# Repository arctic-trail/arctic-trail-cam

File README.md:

# Arctic Trail Cam System

> **Open-source, RF-silent Arctic trail & cabin camera with a 1-way optical fiber diode and `<4mW` cold-boot gatekeeper. A private, pro-bono free-market COTS build. 🇫🇮 Finnish engineering.**
>
> * **GitHub Topics:** `raspberry-pi-5` · `rp2350` · `pico-2` · `hailo-8l` · `plutosdr` · `software-defined-radio` · `troposcatter` · `data-diode` · `fiber-optics` · `bvlos` · `acoustic-sensing` · `micro-doppler` · `ed25519` · `edge-ai` · `cots` · `open-hardware` · `trail-camera` · `finland` · `nordic` · `baltic`
> * **Visual Architecture & Engineering Overview (27-Slide PDF Deck):** [`ARCTIC_TRAIL_CAM_EXECUTIVE_OVERVIEW.pdf`](ARCTIC_TRAIL_CAM_EXECUTIVE_OVERVIEW.pdf)
> * **Complete Illustrated IKEA-Style Build Manual (PDF Booklet):** [`ARCTIC_TRAIL_CAM_BUILD_AND_FIELD_GUIDE.pdf`](ARCTIC_TRAIL_CAM_BUILD_AND_FIELD_GUIDE.pdf)
> * **Sister Project (Autonomous Wilderness Search-and-Rescue Drone, Heated Launch Nest & Maritime USV Autonomy):** [`arctic-trail/karhunkierros-sar-drone`](https://github.com/arctic-trail/karhunkierros-sar-drone)
> * **FIN-LAB COTS Airspace-Safety, Maritime & Corridor Enabler Suite (`FIN-SIG-LIB v1.0` `#4`, `[P12-BELT]` & `[P12-URBAN]` Non-RF Corridor/Bridge/Substation Sensing `#7`, `FIN-LAB-06` `1.85 m` Inshore & `FIN-LAB-06B` `3.60 m` Offshore Sea-State-5 Cable-Inspection USVs `#12`, `[P11-COAST-2KM]` `1–2.5 km` Gimbal-Free Optical Strait Bridge, and `[P21-SVALBARD]` Treeless Permafrost Cairn Kit):** [`pi-diode-trailcam/pi5_sender_node/northern_flank_red_gap_solver.py`](pi-diode-trailcam/pi5_sender_node/northern_flank_red_gap_solver.py)
> * **License:** [`MIT License`](LICENSE)

> **🛠️ PLEASE FORK, BUILD, BREAK & IMPROVE THIS (NO PERMISSION NEEDED)**
> These repositories are **100% open-source (`MIT License`) public-good engineering** for harsh Nordic & Baltic conditions.
> * **No ego, no gatekeeping:** You do **not** need to ask permission to fork this, build a module on your kitchen table, use it for a university course/thesis, or spin a commercial product out of it.
> * **Test logs > theory:** Almost everything here is currently at bench/simulation stage. If you build a €68 acoustic pod, freeze a battery at `-25 °C`, or 3D-print a sub-scale airframe and prove our numbers wrong—**please open a Pull Request or Issue with your real-world data!**
> * **100% Civilian & Legal to Tinker With:** Everything in these repos (weather/wildlife nodes, optical diodes, airport/corridor acoustic logging, SAR navigation, cooperative own-drone soft-net recovery) is strictly civilian and legal for students, hobbyists, and labs to build and test. While the harsh-environment resilience techniques explored here—such as zero-RF optical fiber links, GNSS-denied navigation, acoustic/micro-Doppler drone detection, and low-cost COTS modular packaging—draw technical inspiration from drone and sensor technology widely seen in Ukraine and on public media, the **intended use case of this project is 100% civilian**.

> [!WARNING]
> **PROTOTYPE DISCLAIMER — ACTIVE DEVELOPMENT & BENCHTOP TESTING IN PROGRESS (`v0.9-beta`)**
> * **Under Active Development:** This repository is an **experimental proof-of-concept hardware & software engineering prototype** currently undergoing physical benchtop integration and staged validation.
> * **Validated vs. Target Metrics:** All software/firmware state machines (`Pico 2` Gatekeeper, `Pi 5` sender node, `Ed25519` + `1×2` optical diode UDP pipeline, and `5/5` automated simulation & DRC test suites) are implemented and verified in simulation and Stage 1–3 benchtop bring-up. System performance figures—including the **`6.4–6.8 s` cold-boot latency** (`<150 ms` with SPI Instant-Snap buffer) and **`1.0 to 2.5+ year` (`365–900+ day`) battery life** (at a realistic `10 captures/month` with a drop-in `LiFePO4` / AGM battery, or `4–10+ months` on busy `10 captures/day` trails)—are **engineering design targets and theoretical power/link-budget projections** currently undergoing physical measurement.
> * **Ongoing Defect Tracking & Field Reports:** Hardware, firmware, and mechanical defects discovered during benchtop and outdoor trials are actively being fixed. Measured real-world latency logs, false-alarm soak results, and battery discharge telemetry will be published here as testing progresses.

An off-grid, event-triggered movement-detection and trail camera system (**Arctic Trail Cam System** / `pi-diode-trailcam` & `sky-diode-relay`) designed for remote cabins, hunting grounds, and private forest lands far from internet or cellular coverage. Engineered for year-round operation in harsh Finnish Arctic conditions (`-40°C` to `+50°C`), the system combines milliwatt standby sensing (`Raspberry Pi Pico 2` Gatekeeper), 6-second cold-boot AI vision (`Raspberry Pi 5` + `Sony IMX708 NoIR`), and **physics-enforced one-way optical transmission** (`Ed25519`-signed `1080p` JPEGs sent over `3 mm` moss-buried armored glass fiber or an invisible infrared light beam) with **zero radio emissions (`0.00 W RF`)** at the camera tree.

> [!IMPORTANT]
> **Project Ethos — Private, Pro-Bono Free-Market Engineering ([`MIT License`](LICENSE)):**
> Rather than relying on `$15,000+` proprietary industrial sensors or cloud-tethered cellular cameras that broadcast detectable radio beacons and die in freezing `-30°C` winters, this project explores how **standard commercial off-the-shelf (COTS) components (`$233.37` benchtop / `$598.20` complete turnkey field system including all power supplies, USB/SD adapters, and Cat6/fiber cables)** can be assembled by any cabin owner, hunter, landowner, or researcher:
> 1. **100% Retail COTS Supply Chain:** Built from standard parts on Amazon, Adafruit, DigiKey, Mouser, or Motonet/Verkkokauppa.com in Finland.
> 2. **Zero Cloud Subscriptions & Zero Radio Signature:** No monthly fees, no cellular SIM cards, and zero Wi-Fi/Bluetooth beacons.
> 3. **"IKEA-Simple" Reproducibility:** Every breadboard hole, jumper wire, and enclosure hole-saw cut is illustrated step by step.
> 4. **Single-Source-of-Truth (`SSOT`) Documentation:** Each guide in this repository owns one distinct topic without duplicating tables or instructions across files (see [Documentation Map](#single-source-of-truth-ssot-documentation-map) below).

---

## 1. System Performance & Battery Life Expectations (At a Glance)

Detailed seasonal power models and component-level current draws are maintained in **[`HARDWARE_SPECS_AND_BOM.md`](pi-diode-trailcam/docs/HARDWARE_SPECS_AND_BOM.md#1-system-performance-expectations--cold-boot-latency-spec)**.

| Performance Parameter | Verified / Target Specification | Operating Context |
| :--- | :--- | :--- |
| **Multi-Year Battery Life (Drop-In `12V 15Ah–24Ah` `LiFePO4` / `60Ah` External)** | **At `10 Photos/Month` *(Realistic Cabin / Border Trail)*:**<br>• **`1.5 – 2.5+ Years` (`565 – 900+ Days`)** *(Drop-In `15Ah–24Ah LiFePO4` inside vault)*<br>• **`3.0 – 4.0+ Years`** *(External `60Ah` Battery — self-discharge limited)*<br>**At `10 Photos/Day` (`300/Month` *High-Traffic Trail*):**<br>• **`10 – 16+ Months`** *(`15Ah–24Ah LiFePO4`)* / **`1.8 – 2.5+ Years`** *(`60Ah`)* | At `10 photos/month` (`0.33/day`), active capture energy is negligible (`~0.01 Wh/day`), so total draw with `4–12 mW` Eco Gatekeeper standby is just `~0.15–0.30 Wh/day`. |
| **Battery Life (Standard `12V 12Ah` AGM `[P17]`, `$29` / `€27`)** | **At `10 Photos/Month`:** **`1.0 – 1.3+ Years` (`365 – 480 Days`)** *(3-Season)* / **`9 – 12 Months` (`270 – 365 Days`)** *(Finnish Winter under moss)*<br>**At `10 Photos/Day`:** **`120 – 220+ Days`** | Included baseline `12V 12Ah` sealed AGM battery (`[P17]`) mounted inside the moss-buried `QILIPSU` Base Vault (`[P21]`). |
| **Standby Power (`Domain A` Always-On)** | **`3.8 mW – 12.0 mW`** *(Eco Gatekeeper)* / **`~38 mW`** *(Radar Micro-Sweep)* | `Raspberry Pi 5 [P01]` and `StarTech Fiber Converter [P13]` are **100% physically powered off (`0.00 W`)** by the high-side relay `99.9%` of the time. |
| **Cold-Boot Trigger-to-Photo Latency** | **`6.4 – 6.8 seconds` total** (`0.025 Wh` per capture) | `Pico 2` switches on `Domain B` $\rightarrow$ `Pi 5` boots stripped Linux kernel in `3.8s` $\rightarrow$ captures `1080p` JPEG $\rightarrow$ runs AI detection $\rightarrow$ signs (`Ed25519`) & blasts `3×` over optical fiber $\rightarrow$ cuts power back to `0.00 W`. |
| **Operating Temperature & Weatherproofing** | **`-40°C` to `+50°C` Year-Round (`IP67` / `IP68`)** | Moss-buried `QILIPSU` vault buffers battery at `-2°C to -8°C` in deep winter; `3.6W` PTC window heater clears lens frost in `4.0s`. |
| **Detection & Night-Vision Range** | **`15 m – 60 m` approach** (`25°` oblique trail aim)<br>**`25 m – 80 m` in dense off-trail spruce forest** (`0.6–0.9 m` under-canopy trunk tunnel)<br>**`8 m – 18 m` night IR** (`940 nm` invisible LEDs, zero red glow) | Multi-modal wake cascade (`QMC5883L` magnetometer [`0 dB` wood loss] + `HLK-LD2450` `24 GHz` radar + optional `SM-24` root-mat geophone [`25–60 m` footsteps] & `[P11-AIR]` acoustic diffraction [`35–80 m`] around trunks; see [`ASSEMBLY_GUIDE.md`](pi-diode-trailcam/docs/ASSEMBLY_GUIDE.md#step-61--strap-zone-1-to-the-pine-trunk--bury--insulate-zone-3-underground)). |
| **Link Reach (`Fiber`, `Collimator`, or `Sky-Relay`)** | **`30 m – 10 km`** *(Moss-Buried Armored OS2 Glass Fiber)*<br>**`10 m – 100 m`** *(Water-Strait `1310 nm` Collimator Laser Bridge)*<br>**`200 m – 20 km`** *(All-Weather `2.4 GHz` Troposcatter & Canopy-Bounce Relay — [`sky-diode-relay`](sky-diode-relay/README.md) `Build D`)* | Physical one-way optical data diode (`1×2` optical splitter loopback trick at camera; cabin receiver `TX` port physically unpatched and capped) or one-way `VK7MO` Keyed-FHSS Troposcatter (`+14.1 dB` to `+62.3 dB` all-weather SNR). |

### 1.1 Readiness Matrix, Known Unknowns & Unvalidated Physical Assumptions

To help external evaluators, builders, and researchers assess this project objectively, the table below separates **what has been physically built and bench-verified** from the **key physical unknowns** that remain unproven until freezer and outdoor field trials (`Stages 4–6`) are completed:

| Subsystem / Claim | Built & Verified on Indoor Bench? | Simulated & Unit-Tested? | Field-Validated Outdoors? | Primary Real-World Failure Risk / Unknown | Planned Validation Gate |
| :--- | :---: | :---: | :---: | :--- | :--- |
| **`Pico 2` Gatekeeper + `GY-271` (`0x2c`) + `Pi 5` + `IMX708` + `1×2` Optical Fiber Diode (`Stages 1–3`)** | **Yes** (`Photos 1–72` live bench build) | **Yes** (`5/5` suites) | **No** (indoor bench only) | Mechanical vibration loosening breadboard jumpers or ZIF ribbons during transport if the 3-step `Permatex 81158` silicone + `3M` block lock is skipped. | **Stage 4–5:** Enclosure integration, vibration lock, and `48-hour` outdoor soak. |
| **`6.4 – 6.8 s` Cold-Boot Trigger-to-Photo Latency** | **Partial** (standard Raspbian boot verified; stripped initramfs modelled) | **Yes** | **No** | Standard Debian Bookworm boots in `~12–18 s`; achieving `6.4 s` in hardware requires tuning the stripped kernel/initramfs (`quiet fastboot`) and verifying that cold `-20 °C` battery internal resistance ($I\cdot R$ drop) does not brown out the `5V/5A` buck during `Pi 5` + `StarTech` inrush. | **Stage 5 & Freezer Gate:** Oscilloscope/multimeter inrush voltage check at `-18 °C` (`4-hour` freezer test). |
| **`1.0 – 2.5+ Year` Battery Life & `3.8 mW` Standby Draw** | **No** (power switches `[P12]` in hand; long-term discharge modelled) | **Yes** (seasonal power model) | **No** | Elevated quiescent leakage in budget buck converters (`DIANN` / `5A USB-C` buck), frequent false wakes from wind-blown branches on the `24 GHz` radar (`HLK-LD2450`), or unburied `-30 °C` AGM electrolyte freezing can cut real battery life by `50–80%`. | **Stage 5:** Multimeter microamp standby measurement across `Domain A/B` + `48-hour` wind false-alarm soak. |
| **`sky-diode-relay` `Build D` (`200 m – 20 km` NLOS Troposcatter / Canopy-Bounce)** | **Parts 100% In Stock** (`PlutoSDR`, `SE2576L` PA, `SKY65405` LNA, `VBF-2435+`, `HG2414P`) | **Yes** (`24/24` channel & FEC suites) | **No** (`0 km` outdoor RF test to date) | Real granite ridge diffraction profiles, wet heavy snow on conifer needles (`ITU-R P.833`), or local `2.4 GHz` noise floors higher than modelled can reduce the theoretical `+14.1 dB` worst-case SNR margin at `20 km`. | **Build D Field Trial:** Progressive `500 m` $\to$ `2 km` $\to$ `10–20 km` NLOS link-margin walk test. |
| **`[P11-AIR]` Acoustic/Micro-Doppler & `[P12-BELT]` Corridor Classifiers** | **No** (algorithmic & signature models in `northern_flank_red_gap_solver.py`) | **Yes** (`FIN-SIG-LIB v1.0`) | **No** | Heavy wind roar in pine crowns (`> 12 m/s`), freezing rain on MEMS microphone ports (`IM69D130`), or highway traffic acoustics can raise false-alarm rates above the modelled `≤ 25%` ceiling. | **Acoustic Field Gate:** Outdoor winter recordings with wind-muff hydrophobic membranes. |

---

## 2. Device in Context: 3-Zone Pine Tree Unit & `200 m – 20 km` Troposcatter / Beam Relay

Detailed exterior/interior cutaway plates for **Device 1 (`Zone 1` Camera/Radar Pod)**, **Device 2 (`Zone 3` Base Vault)**, **Device 3 (Cabin & Woods Collectors)**, and the **Scenario A / B1 / B2 / B3** deployment comparison are included in **[`ASSEMBLY_GUIDE.md`](pi-diode-trailcam/docs/ASSEMBLY_GUIDE.md)**.

### 2.1 The 3-Zone Covert Split-Pod Camera Unit on a Forest Pine Tree

* **Zone 1 (Top — `2.0 m` High in Pine Bark Crevice):** Fist-sized `Hammond 1591BSBK` (`112 × 62 × 31 mm`, factory `IP54` sealed with a perimeter `Permatex 81158` lid-channel gasket, or drop-in `Hammond 1554EGY` factory `IP68`) pod with **only one circular `20 mm` (`[T06]` cone step bit) or `28 mm` (`[T05]` hole saw) glass window** (`IMX708` camera locked to `AfMode=0, LensPosition=0.5` hyperfocal focus + black neoprene foam anti-glare baffle + `2× 940 nm` stealth IR LEDs + `39-Ohm 5W` [`3.69 W` @ `12V`] de-icer) and an internal `HLK-LD2450` `24 GHz` radar shooting cleanly through the solid, uncut lower ABS wall.
* **Zone 2 (Middle — `2.0 m` Trunk Cord):** Shielded `Arducam CSI-to-HDMI` (`2.0 m`) + 4-wire radar/heater umbilical wrapped in `Gear Aid Camo Form` matte bark tape tucked into a natural vertical bark groove.
* **Zone 3 (Bottom — Buried `20–30 cm` Underground & Foam-Insulated at Tree Roots):** Waterproof `QILIPSU IP67` (`285 × 195 × 130 mm`) vault housing the wall-to-wall `12V 12Ah` battery (`[P17]`), `Pico 2` Gatekeeper (`[P07]`), `5V` buck/relay power switches (`[P12]`), `Raspberry Pi 5` (`[P01]`), and `1310 nm` `StarTech` Media Converter + `1×2` Optical Splitter Diode (`[P13]`–`[P15]`).
  * **Cold-Weather Survival WITH vs. WITHOUT Underground Burial & Foam Insulation:** The tree-mounted **Zone 1 Micro-Pod** contains only solid-state silicon + the `3.69 W` ceramic window de-icer (`[P12-HEAT]`) and operates in open air down to **`-35°C to -40°C`**. For the **Zone 3 Base Vault**: **WITHOUT underground burial or foam insulation** (sitting above ground in open air with standard `12Ah` AGM `[P17]`), reliable operation is limited to **`-15°C to -20°C`** (`45%–55%` battery capacity; risk of `Pi 5` boot brownout or electrolyte freeze below `-22°C`, or **`-25°C to -28°C`** if fitted with the `10–20 mm` foam liner + `[P21-FROST]` supercap buffer on bare rock). **WITH `20–30 cm` underground burial + `10–20 mm` closed-cell XPS/neoprene foam insulation + moss/snow cover**, geothermal subsoil warmth keeps the internal battery bay at **`-2°C to -8°C`** even when outside air plunges to **`-35°C to -40°C`** (**`-45°C`** under `30+ cm` snowpack), preserving **`85%–92%` battery capacity** (`1.2–2.5+ years` with `LiFePO4`).

### 2.2 The `200 m – 20 km` Non-Line-of-Sight Troposcatter & Water-Crossing Beam System ([`sky-diode-relay`](sky-diode-relay/README.md))

* **Ordered Production Baseline (`Build D` — `200 m to 20 km` All-Weather `2.4 GHz` Troposcatter, Hydrometeor & Canopy-Bounce Relay, `$1,341.94` parts subtotal, `~35–45 min` zero-solder assembly):** Uses **Analog Devices `ADALM-PLUTO` SDRs**, a **Skyworks `SE2576L-EK1` `1.0 W` (`+30 dBm`) PA (`PA_EN` driven strictly at `3.3 V` from `Pico 2 GP3`)**, a **Skyworks `SKY65405-21EK1` (`1.2 dB NF`) LNA (`VEN` driven strictly at `3.3 V` from `Pico 2 3V3_OUT`)**, **Mini-Circuits `VBF-2435+` (`2370–2500 MHz`) coaxial bandpass filters**, and **L-com `HG2414P` (`14 dBi`) outdoor flat-panel antennas** to bounce `VK7MO` coherent lock-in frames (`+55.8 dB` processing gain) off lower-troposphere refractivity gradients, rain/snow clouds, and forest canopies over granite hills (`+14.1 dB` to `+62.3 dB` SNR across all 5 Finnish weather regimes). Protected by a **6-layer electronic anti-jamming stack** that hops into out-of-ISM guard bands (`2380.373 MHz` & `2487.818 MHz`) outside consumer Wi-Fi/drone jammers.
  * **⚠️ Regulatory Disclaimer & `--civilian-eu-compliant` Software Flag (Zero Hardware Changes):** Operating `Build D` at full `1.0 W` (`+42.5 dBm` / `17.8 W` EIRP) or hopping into out-of-ISM guard bands (`2370–2400 MHz` / `2483.5–2500 MHz`) **requires a Traficom experimental/test radio license, public-safety / emergency authority authorization, or Amateur Radio permit (`13 cm` band, `2300–2450 MHz`)**. For **license-exempt peacetime civilian operation** under Traficom Regulation 15 / EU ETSI EN 300 328, pass **`--civilian-eu-compliant`** (`civilian_eu_compliant=True`) to `sky_transmitter.py` and `sky_receiver.py`: this restricts all FHSS carrier hops strictly inside **`2400.0–2483.5 MHz`** (`2402–2480 MHz`) and disables/attenuates the PA (`pa_gate_gp3=0`, `+7.5 dBm` SDR output) so total radiated power is capped at **`<= +20.0 dBm` (`100 mW` EIRP)** while still bridging multi-kilometer NLOS forest paths via `VK7MO`'s `+55.8 dB` coherent processing gain.
* **Short-Range Optical Beam (`Scenario B2` — `10 m to 100 m` Across a Lake Strait or Road):** Two shore-mounted `1310 nm` fiber lens collimators (**Thorlabs `F220FC-1310`**) convert the fiber signal into a pencil-thin, invisible infrared laser beam across water channels where boats or winter ice prevent laying cable (with optical reference builds `A/B/C` also supported in [`sky-diode-relay`](sky-diode-relay/README.md)).

### 2.3 The Cabin Collector Hub & 3D Evidence Console ([`dashboard_server.py`](pi-diode-trailcam/collector_hub/dashboard_server.py) / [`ui/index.html`](pi-diode-trailcam/collector_hub/ui/index.html))

* **100% Offline Local Browser Console (`http://localhost:8080` / `8123`):** Streams `Ed25519`-verified JPEGs (`DD\x02` chunks), AI bounding boxes (`Hailo-8L` / `YOLOv8n ONNX`), `<150 ms` `Pico 2` SPI First-Frame Instant-Snap PIP insets, and 6-cell `Pico 2` sensor telemetry (`MAG ΔB`, `SEISMIC RMS`, `RADAR DIST/SPD`, `NODE TEMP`, `UPTIME`, `PROFILE`) alongside an interactive 3D topographical terrain map (`Nuuksio`, `Saimaa Archipelago`, `Koli`, `Inari Lapland`, or custom `GeoJSON`/`DEM`) and real-time 4-channel sensor waveforms.

---

## 3. Build Cost Tiers (`$233` to `$598`) & Step-by-Step IKEA Manuals

The complete itemized parts schedule (`[P01]`–`[P24]`), workshop tool list (`[T01]`–`[T12]`), and 5-hole enclosure drilling table live exclusively in **[`HARDWARE_SPECS_AND_BOM.md`](pi-diode-trailcam/docs/HARDWARE_SPECS_AND_BOM.md)**.

| Build Tier | Parts Included | Total (USD) | Approx. (EUR) | Where to Start |
| :--- | :--- | :---: | :---: | :--- |
| **Tier 1A — Indoor Core Benchtop Kit (`Stages 1–2`)** | `[P01]`, `[P02]`, `[P04]`–`[P10]`, `[P23]`, `[P24]` | **`$233.37`** | **`~€215`** | **[IKEA Manual Part 1 (`Stages 1–2`)](pi-diode-trailcam/docs/BENCHTOP_QUICKSTART_GUIDE.md)** |
| **Tier 1B — Indoor Benchtop + Optical Fiber Diode (`Stages 1–3`)** | Tier 1A + `[P13]`–`[P16]`, `[P19]` | **`$402.67`** | **`~€370`** | **[IKEA Manual Part 1 (`Stage 3`)](pi-diode-trailcam/docs/BENCHTOP_QUICKSTART_GUIDE.md#stage-3-snap-together-the-1-way-optical-fiber-data-diode-p13p16-p19)** |
| **Tier 2A — 3-Zone Weatherproof Field Camera Node Only (`Stages 1–6`)** | Field Node `[P01]`–`[P24]` (excl. Cabin RX, `30m` spool & laptop adapter) | **`$497.25`** | **`~€457`** | **[IKEA Manual Part 2 (`Stages 4–5`)](pi-diode-trailcam/docs/ASSEMBLY_GUIDE.md)** |
| **Tier 2B — Complete Turnkey System (`Field Node + 30m Fiber + Cabin RX + All Cables/Adapters`)** | **All `[P01]`–`[P24]` Parts** | **`$598.20`** | **`~€550`** | **[IKEA Manual Part 2 (`Stage 6`)](pi-diode-trailcam/docs/ASSEMBLY_GUIDE.md#stage-6-tree-installation-collector-setup--operating-the-system-in-the-field)** |

---

## 4. Single-Source-of-Truth (`SSOT`) Documentation Map

Every document in this repository owns **one distinct responsibility** with zero duplicated tables:

| Document | Single-Source-of-Truth (`SSOT`) Responsibility |
| :--- | :--- |
| **[`ARCTIC_TRAIL_CAM_EXECUTIVE_OVERVIEW.pdf`](ARCTIC_TRAIL_CAM_EXECUTIVE_OVERVIEW.pdf)** | **27-Slide Visual Architecture & Engineering Overview Deck (PDF):** End-to-end visual walk-through of the 3-zone camera pod, wake cascade, optical diode, `Build D` relay, BOM tiers, and validation roadmap. |
| **[`ARCTIC_TRAIL_CAM_BUILD_AND_FIELD_GUIDE.pdf`](ARCTIC_TRAIL_CAM_BUILD_AND_FIELD_GUIDE.pdf)** | **Illustrated Master Build Booklet** (compiled printable PDF of Stages 1–6 + 1:1 vector drilling templates). |
| **[`HARDWARE_SPECS_AND_BOM.md`](pi-diode-trailcam/docs/HARDWARE_SPECS_AND_BOM.md)** | **Parts (`[P01]`–`[P24]`), Tools (`[T01]`–`[T12]`), Retail Prices, Seasonal Battery Life Models & 5-Hole Drilling Schedule.** |
| **[`BENCHTOP_QUICKSTART_GUIDE.md`](pi-diode-trailcam/docs/BENCHTOP_QUICKSTART_GUIDE.md)** | **IKEA Manual Part 1 (`Stages 1–3`):** Real-photo benchtop assembly (`Photos 1–72`), SD/Pico flashing, breadboard wiring (`W1`–`W7`), and optical diode test. |
| **[`ASSEMBLY_GUIDE.md`](pi-diode-trailcam/docs/ASSEMBLY_GUIDE.md)** | **IKEA Manual Part 2 (`Stages 4–6`):** Enclosure hole-saw drilling, glass sealing, solid matte forest-green painting, `12V` battery wiring, `Device 1–3` cutaways, `Scenario A / B1 / B2 / B3` field topologies & air-shipping guide. |
| **[`WIRING_PINOUT.md`](pi-diode-trailcam/docs/WIRING_PINOUT.md)** | **Electrical Pinout & Voltage Schedule:** Exact GPIO, I2C, UART, ADC, and power-domain pin assignments. |
| **[`pi-diode-trailcam/README.md`](pi-diode-trailcam/README.md)** | **Software CLI & Collector Hub Reference:** `sender_node.py`, `receiver_hub.py`, `dashboard_server.py`, and `generate_keys.py`. |
| **[`FIELD_TESTING_AND_VALIDATION_GUIDE.md`](pi-diode-trailcam/docs/FIELD_TESTING_AND_VALIDATION_GUIDE.md)** | **Field Acceptance Protocol:** 20-walk detection matrix, night `940 nm` zero-glare test, and 48-hour (`192-event`) unattended soak checklist. |
| **[`PROJECT_DECISIONS_AND_ROADMAP.md`](PROJECT_DECISIONS_AND_ROADMAP.md)** | **Architecture Trade-Off Decisions (`Decisions 1–9`) & Codebase Audit Log:** Engineering rationale, field vibration-locking rules, and historical defect remediation record. |
| **[`technical_architecture_engineering_specification.md`](technical_architecture_engineering_specification.md)** | **Wire Protocol & Cryptographic Spec:** Byte-level layout of `DD\x01` telemetry packets, `DD\x02` FEC JPEG chunks, `Ed25519` signatures, and `ChaCha20-Poly1305`. |
| **[`sky-diode-relay/README.md`](sky-diode-relay/README.md)** | **All-Weather `200 m – 20 km` Troposcatter & Optical Relay (`sky-diode-relay`):** Ordered `Build D` (`2.4 GHz` Troposcatter/Canopy-Bounce), 6-layer anti-jamming FHSS lock-in, `Hamming(8,4)` erasure FEC, and [`DESIGN_EVOLUTION_AND_STABILITY_RECORD.md`](sky-diode-relay/docs/DESIGN_EVOLUTION_AND_STABILITY_RECORD.md). |
| **[`arctic-trail/karhunkierros-sar-drone`](https://github.com/arctic-trail/karhunkierros-sar-drone)** | **Sister Project — Autonomous Wilderness SAR Drone & "Digital Wilderness Hut" Guidance System:** Reuses 100% of this camera & collector stack as a passive 48h `0.00 W` RF trail post paired with a GNSS-independent `Holybro X500 V2` aerial lantern rescue drone (`~€1,189–€1,329` COTS). |

---

## 5. Automated Software, Protocol & Channel Simulation Suites

*(Note: These automated suites validate software state machines, `Ed25519` cryptography, durable disk persistence, pagination, and Monte-Carlo channel models in deterministic software simulation; physical hardware acceptance tests are defined in [`FIELD_TESTING_AND_VALIDATION_GUIDE.md`](pi-diode-trailcam/docs/FIELD_TESTING_AND_VALIDATION_GUIDE.md).)*

```bash
# 1. Run the interactive no-hardware benchtop simulation (generates a signed alert + opens live dashboard):
python3 pi-diode-trailcam/run_mock_demo.py

# 2. Run all trailcam unit, firmware, resilience, and quality-assessment regression suites:
python3 pi-diode-trailcam/tests/test_dual_node_simulation.py
python3 pi-diode-trailcam/tests/test_pico_firmware_simulation.py
python3 pi-diode-trailcam/tests/test_enhanced_resilience.py
python3 pi-diode-trailcam/tests/test_quality_assessment_remediations.py

# 3. Run all 24 sky-diode-relay 20km all-weather troposcatter, anti-jamming, civilian-EU mode, and FEC tests:
python3 -B sky-diode-relay/tests/test_sky_relay_simulation.py
```

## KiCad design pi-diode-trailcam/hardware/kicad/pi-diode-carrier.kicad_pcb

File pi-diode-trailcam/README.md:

# `pi-diode-trailcam` — Software Stack & CLI Reference

> **Single-Source Documentation Notice:** System architecture, hardware BOMs, and step-by-step assembly instructions are maintained in a single location to avoid duplication:
> * **Project Overview & SSOT Documentation Map:** [`../README.md`](../README.md)
> * **Complete Illustrated Build & Field Manual (PDF):** [`../ARCTIC_TRAIL_CAM_BUILD_AND_FIELD_GUIDE.pdf`](../ARCTIC_TRAIL_CAM_BUILD_AND_FIELD_GUIDE.pdf)
> * **Part 1 — Indoor Benchtop Assembly (`Stages 1–3`, `Photos 1–58`):** [`docs/BENCHTOP_QUICKSTART_GUIDE.md`](docs/BENCHTOP_QUICKSTART_GUIDE.md)
> * **Part 2 — Enclosure Build, Camouflage & Tree Deployment (`Stages 4–6`):** [`docs/ASSEMBLY_GUIDE.md`](docs/ASSEMBLY_GUIDE.md)
> * **Parts, Tools & Cold-Weather Power Schedule (`[P01]`–`[P24]`, `[T01]`–`[T12]`):** [`docs/HARDWARE_SPECS_AND_BOM.md`](docs/HARDWARE_SPECS_AND_BOM.md)
> * **Electrical Pinout & Breadboard Coordinate Schedule:** [`docs/WIRING_PINOUT.md`](docs/WIRING_PINOUT.md)

---

## Core Software Entry Points

| File | Role & Capabilities |
| :--- | :--- |
| [`pico_gatekeeper/main.py`](pico_gatekeeper/main.py) | Always-on sensor polling (`QMC5883L` + `HLK-LD2450` + optional `SM-24`/`ADS1115`), automatic sensor profile detection (`PROFILE_FULL_TRIPLE`, `PROFILE_MAG_RADAR_DUTY`, `PROFILE_BENCH_MAG_ONLY`), parallel staggered PTC lens de-icing ($t = 0.25\text{..}4.25\text{ s}$), `UART1` telemetry (`TRIG,...,UPTIME_S=`), and $3 \times 25\text{ ms}$ EMI-debounced `DONE` power cutoff (`GP17`/`GP2`). |
| [`pi5_sender_node/sender_node.py`](pi5_sender_node/sender_node.py) | Cold-boot `Picamera2` capture (locked hyperfocal `AfMode=0, LensPosition=0.5`), `1000BASE-T` carrier-lock polling, multi-line UART frame sync, `Hailo-8L` $\rightarrow$ CPU YOLOv8n ONNX (`NMSBoxes`) $\rightarrow$ Motion ROI fallback chain, `Ed25519` signing, 8-byte `nonce` chunk headers, and $3\times$ paced UDP carousel transmission (`10.10.0.100:5514`). |
| [`pi5_sender_node/install_pi5_fastboot.sh`](pi5_sender_node/install_pi5_fastboot.sh) | Idempotent Raspberry Pi OS Bookworm fastboot provisioning (`dtparam=uart0=on`, `enable_uart=1`, static ARP injection, `diode-node.service` registration, read-only `OverlayFS`). |
| [`pi5_sender_node/generate_keys.py`](pi5_sender_node/generate_keys.py) | Per-node `Ed25519` keypair generator (`--node`, `--write-node-key`, `--register-hub`) populating `node_key.json` and `authorized_nodes.json`. |
| [`collector_hub/receiver_hub.py`](collector_hub/receiver_hub.py) | Passive UDP `5514` listener, `Ed25519` verification, 8-byte `nonce` chunk reassembly, Pass 2/3 corrupt-chunk SHA-256 repair, persistent `seen_nonces.jsonl` anti-replay cache, circular disk retention (`--max-alerts`), and Dead-Drop bundle export/verification (`--export-bundle`, `--verify-bundle`). |
| [`collector_hub/dashboard_server.py`](collector_hub/dashboard_server.py) | Local Web UI server (`127.0.0.1:8123` default) with `?since_idx=` alert pagination, `os.path.commonpath` traversal protection, and forensic evidence ZIP export. |
| [`collector_hub/ui/index.html`](collector_hub/ui/index.html) | Browser dashboard rendering verified JPEGs (`/alerts/<file>.jpg`) and AI bounding-box overlays alongside 3D terrain telemetry. |
| [`collector_hub/subghz_nlos_relay.py`](collector_hub/subghz_nlos_relay.py) | One-way Sub-GHz (`868 MHz` EU / `915 MHz` US) FHSS / LoRa woods-vault-to-farmhouse bridge (`--mode tx-vault` / `--mode rx-farmhouse`). |
| [`run_guided_bench_doctor.py`](run_guided_bench_doctor.py) | Automated benchtop hardware doctor (`--self-test`, `--start-hub`, `--open-browser`): probes Pico 2 USB/`I2C0` (`0x0d`), checks Pi SSH & camera, prints pin-exact breadboard hole troubleshooting (`Hole j5`, `Hole j3`, `Hole a6`, `Hole a7`, `Hole a11`, `Hole a4`, `Hole a13`, `Hole f24`–`Hole f27`), and launches the Collector Hub + Live Dashboard. |
| [`run_freezer_soak_acceptance.py`](run_freezer_soak_acceptance.py) | Stage 5 `-18 °C` freezer soak & cold-start acceptance runner (`--self-test`, `--journal-dir`, `--max-temp-c -10.0`, `--min-frames 5`): audits `Ed25519` `.sig.json` receipts, `SHA-256` JPEG integrity, `TEMP=` telemetry, and fail-closed production key enforcement. |
| [`run_mock_demo.py`](run_mock_demo.py) | Self-contained synthetic end-to-end verification of `Ed25519` signing, 8-byte `nonce` chunking, and UDP reconstruction. |

---

## Quick CLI Commands

```bash
# 1. Start the Cabin Collector Receiver & Live Web Dashboard (http://127.0.0.1:8123):
python3 collector_hub/receiver_hub.py
python3 collector_hub/dashboard_server.py --port 8123

# 2. Run Headless Dead-Drop Vault Mode (circular disk retention + portable ZIP export/verify):
python3 collector_hub/receiver_hub.py --max-alerts 1000 --out-dir ./verified_alerts
python3 collector_hub/receiver_hub.py --out-dir ./verified_alerts --export-bundle ./dead_drop_alerts_export.zip
python3 collector_hub/receiver_hub.py --verify-bundle ./dead_drop_alerts_export.zip

# 3. Provision Unique Production Ed25519 Node Keys & Fast-Boot Service on Raspberry Pi 5:
python3 pi5_sender_node/generate_keys.py CAMERA-NORTH-01
sudo bash pi5_sender_node/install_pi5_fastboot.sh CAMERA-NORTH-01

# 4. Run Stage 5 -18 °C Freezer Soak Acceptance Audit:
python3 run_freezer_soak_acceptance.py --self-test
python3 run_freezer_soak_acceptance.py --journal-dir ./verified_alerts --max-temp-c -10.0 --min-frames 5
```

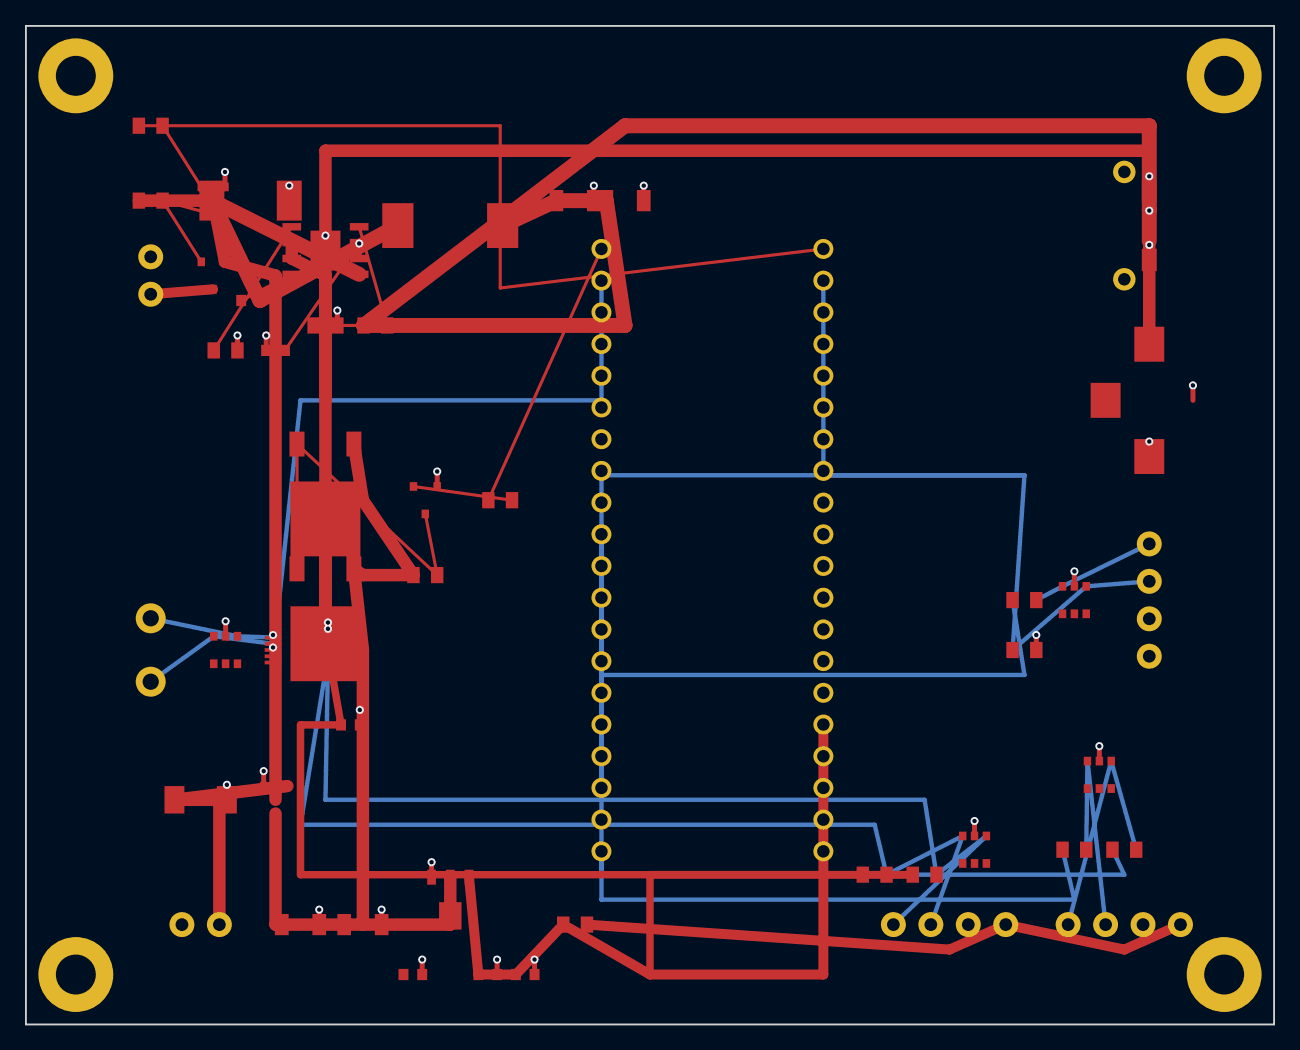
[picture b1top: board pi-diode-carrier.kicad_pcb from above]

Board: 4 copper layers, 100.0 x 80.0 mm, 49 parts (0 on the bottom side), 32 nets.

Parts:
C1, C2: 10uF-50V; C_1206
C3, C4: 47uF-16V; C_1206
C5, C6, C7, C8, C9: 0.1uF-50V; C_0603
C10: 10nF-50V; C_0603
D1: SMBJ15CA; DO-214AA_SMB
D2, D3, D4, D5: USBLC6-2SC6; SOT-23-6
D6: SS54-E3; DO-214AB_SMC
FB1, FB2, FB3: 220R-2A; L_0805
J1: Micro-Fit-2P-Batt; CONN-TH_2P-P3.00mm
J2: Micro-Fit-4P-Mag; CONN-TH_4P-P3.00mm
J3: Micro-Fit-4P-Radar; CONN-TH_4P-P3.00mm
J4: Micro-Fit-4P-Pi5; CONN-TH_4P-P3.00mm
J5: USB-C-5V-5A; USB-C-SMD
J6: DC-Barrel-2.1mm; DC-005_SMD
J7: Micro-Fit-2P-Deice; CONN-TH_2P-P3.00mm
L1: 10uH-6.5A; IND-SMD_10x10mm
Q1, Q3: AO3401A; SOT-23
Q2A, Q2B: AOD403; TO-252
Q4, Q5: MMBT2222A; SOT-23
R1, R6, R7, R8: 10k-1%; R_0805
R2, R9, R10: 1k-1%; R_0805
R3, R4: 4.7k-1%; R_0805
R5: 53.6k-1%; R_0805
R11: 100k-1%; R_0805
TB1: Screw-Terminal-2P; TERM-5.08mm-2P
U1: HT7533-1; SOT-89
U2: RP2040-Pico-Socket; DIP-40
U3: TPS54560BDDAR; SOIC-8-EP
U4: ADS1115IDGSR; VSSOP-10

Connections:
+3V3_ALWAYS_ON: C5.1, C6.1, C8.1, D4.5, D5.5, FB1.1, J4.3, R3.1, R4.1, U1.3, U2.36, U2.39, U4.8
+3V3_SENSORS: D2.5, D3.5, FB1.2, J2.1, J3.1
+5V_PI5: C3.1, C4.1, J5.2, J5.4, L1.2, R5.1
+12V_BATT: C1.1, C2.1, C7.1, Q1.3, Q2A.2, Q2B.2, Q3.2, R7.1, R8.1, U1.2, U1.4
+12V_DEICE: J7.1, Q3.3
+12V_RAW: D1.1, J1.1, Q1.2
+12V_SWITCHED: J6.1, Q2A.3, Q2B.3, U3.2, U3.3
GATE_CTRL_DEICE: R10.1, U2.21
GATE_CTRL_DOMAIN_B: R9.1, U2.20
GEOPHONE_ALERT: U2.19, U4.2
GEOPHONE_N: D4.3, D4.4, TB1.2, U4.5
GEOPHONE_P: D4.1, D4.6, TB1.1, U4.4
GND: C1.2, C2.2, C3.2, C4.2, C5.2, C6.2, C7.2, C8.2, C10.1, D1.2, D2.2, D3.2, D4.2, D5.2, D6.2, J1.2, J2.2, J3.2, J4.4, J5.1, J5.3, J5.5, J5.6, J5.7, J6.2, J6.3, J7.2, Q1.1, Q4.2, Q5.2, R1.2, R6.2, R11.2, U1.1, U2.3, U2.8, U2.13, U2.18, U2.23, U2.28, U2.33, U2.38, U3.7, U3.9, U4.1, U4.3, U4.6, U4.7
I2C0_SCL: D2.3, D2.4, J2.4, R4.2, U2.7, U4.10
I2C0_SDA: D2.1, D2.6, J2.3, R3.2, U2.6, U4.9
NC: U2.5, U2.9, U2.10, U2.12, U2.14, U2.15, U2.16, U2.17, U2.24, U2.25, U2.26, U2.27, U2.29, U2.30, U2.31, U2.32, U2.34, U2.35, U2.37, U2.40
PI5_DONE: D5.3, D5.4, J4.2, R1.1, U2.4, U2.22
PI5_UART_RX: D5.1, D5.6, J4.1, R2.2
Q2_GATE: Q2A.1, Q2B.1, Q4.3, R7.2
Q3_GATE: Q3.1, Q5.3, R8.2
Q4_BASE: Q4.1, R9.2
Q5_BASE: Q5.1, R10.2
TELEMETRY_TX: R2.1, U2.11
TPS_BOOT: C9.1, U3.1
TPS_COMP: C10.2, U3.6
TPS_FB: R5.2, R6.1, U3.5
TPS_RT: R11.1, U3.4
TPS_SW: C9.2, D6.1, L1.1, U3.8
UART0_RADAR_RX: D3.1, D3.6, FB2.2, J3.3
UART0_RADAR_TX: D3.3, D3.4, FB3.2, J3.4
UART0_RX_PICO: FB3.1, U2.2
UART0_TX_PICO: FB2.1, U2.1

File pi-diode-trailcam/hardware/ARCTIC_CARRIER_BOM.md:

# Carrier component inventory — unvalidated

This inventory supports the [unreleased carrier study](CARRIER_BOARD_DESIGN_SPEC.md). It is not a manufacturing release. Part limits, footprints, substitutions, reference designators and the complete circuit must be reconciled before procurement. System-level purchasing is maintained in the [system BOM](../docs/HARDWARE_SPECS_AND_BOM.md).

## 1. Active Semiconductors & Integrated Circuits

| Item | RefDes | Description | Manufacturer | Manufacturer Part Number (MPN) | Package | Mouser / Farnell Order No. |
|---|---|---|---|---|---|---|
| 1 | `U1` | Ultra-Low-Quiescent 3.3V LDO Regulator ($I_q = 4\,\mu\text{A}$, 250mA) | Holtek | **HT7333-A** (or TI `TPS7A0233PDBVR`) | SOT-89 / SOT-23-5 | Mouser: `595-TPS7A0233PDBVR` |
| 2 | `U2` | Dual-Core ARM Cortex-M0+ Microcontroller Module (RP2040) | Raspberry Pi | **Raspberry Pi Pico H** | 40-Pin Castellated / DIP | Farnell: `3874378` |
| 3 | `U3` | Automotive 60V 5A Step-Down Buck Converter (>92% Efficiency) | Texas Instruments | **TPS54560BDDAR** | SO-8 PowerPAD | Mouser: `595-TPS54560BDDAR` |
| 4 | `U4` | 16-Bit Low-Power Precision ADC with Internal Reference | Texas Instruments | **ADS1115IDGSR** | VSSOP-10 | Mouser: `595-ADS1115IDGSR` |
| 5 | `Q1, Q3` | P-Channel Enhancement MOSFET ($-20\text{V}$, $-4.2\text{A}$, $R_{\text{DS(on)}} < 52\,\text{m}\Omega$) | Diodes Inc. | **DMG2305UX-7** | SOT-23 | Mouser: `621-DMG2305UX-7` |
| 6 | `Q2A, Q2B`| Dual N-Channel Power MOSFET ($40\text{V}$, $50\text{A}$, $R_{\text{DS(on)}} < 8\,\text{m}\Omega$) | Alpha & Omega | **AOD4184A** (or Onsemi `NTD4906N`) | TO-252 (DPAK) | Mouser: `863-NTD4906NT4G` |
| 7 | `Q4, Q5` | NPN General Purpose Bipolar Transistor ($40\text{V}$, $600\text{mA}$) | Nexperia | **PMBT2222A,215** | SOT-23 | Mouser: `771-PMBT2222A-T/R` |
| 8 | `D1` | 600W Bidirectional Transient Voltage Suppressor (TVS) | Littelfuse | **SMBJ15CA** | SMB (DO-214AA) | Mouser: `576-SMBJ15CA` |
| 9 | `D2..D5` | Low-Capacitance ($3.5\,\text{pF}$) Rail-to-Rail ESD Protection Array | STMicroelectronics | **USBLC6-2SC6** | SOT-23-6 | Mouser: `511-USBLC6-2SC6` |
| 10 | `D6` | 40V 5A Schottky Barrier Rectifier (Freewheeling for Buck) | Vishay | **SS54-E3/57T** | SMC (DO-214AB) | Mouser: `625-SS54-E3` |

---

## 2. Passive Components (Inductors, Capacitors & Resistors)

| Item | RefDes | Value / Description | Manufacturer | Manufacturer Part Number (MPN) | Package | Supplier |
|---|---|---|---|---|---|---|
| 11 | `L1` | $10\,\mu\text{H}$, $6.5\text{A}$ Shielded Power Inductor (Buck Output) | Wurth Elektronik | **744314101** | $10.5 \times 10\,\text{mm}$ | Mouser: `710-744314101` |
| 12 | `C1, C2` | $10\,\mu\text{F}$, $50\text{V}$ X7R Ceramic Capacitor (12V Input) | Murata | **GRM31CR71H106KA12L** | 1206 | Mouser: `81-GRM31CR71H106KA2L` |
| 13 | `C3, C4` | $47\,\mu\text{F}$, $16\text{V}$ X7R Ceramic Capacitor (5V Buck Output) | TDK | **C3216X7R1C476M160AC** | 1206 | Mouser: `810-C3216X7R1C476M` |
| 14 | `C5..C8` | $0.1\,\mu\text{F}$, $50\text{V}$ X7R Decoupling Capacitor | Murata | **GRM188R71H104KA93D** | 0603 | Mouser: `81-GRM188R71H104KA9D` |
| 15 | `R1` | $10\,\text{k}\Omega$, $1\%$, $0.125\text{W}$ Thick Film Resistor (Pi 5 Handshake) | Vishay | **CRCW080510K0FKEA** | 0805 | Mouser: `71-CRCW080510K0FKEA` |
| 16 | `R2` | $1\,\text{k}\Omega$, $1\%$, $0.125\text{W}$ Thick Film Resistor (UART Isolation) | Vishay | **CRCW08051K00FKEA** | 0805 | Mouser: `71-CRCW08051K00FKEA` |
| 17 | `R3, R4` | $4.7\,\text{k}\Omega$, $1\%$ Pull-Up Resistors (I2C0 SDA/SCL) | Vishay | **CRCW08054K70FKEA** | 0805 | Mouser: `71-CRCW08054K70FKEA` |
| 18 | `FB1..FB3`| Ferrite Bead $220\,\Omega$ @ $100\text{MHz}$, $2\text{A}$ (Noise Suppression) | Murata | **BLM21PG221SN1D** | 0805 | Mouser: `81-BLM21PG221SN1D` |

---

## 3. Industrial Latching Connectors & Terminals

| Item | RefDes | Description | Manufacturer | Manufacturer Part Number (MPN) | Mouser / Farnell Order No. |
|---|---|---|---|---|---|
| 19 | `J1` | 12V Battery Input Header (Molex Micro-Fit 3.0, 2-Pin, Right Angle) | Molex | **43650-0200** | Mouser: `538-43650-0200` |
| 20 | `J2` | I2C0 Sensor Bus Header (Molex Micro-Fit 3.0, 4-Pin, Right Angle) | Molex | **43650-0400** | Mouser: `538-43650-0400` |
| 21 | `J3` | 24 GHz Radar UART Header (Molex Micro-Fit 3.0, 4-Pin, Right Angle)| Molex | **43650-0400** | Mouser: `538-43650-0400` |
| 22 | `J4` | Raspberry Pi 5 Telemetry / Done Header (Micro-Fit 3.0, 4-Pin) | Molex | **43650-0400** | Mouser: `538-43650-0400` |
| 23 | `J5` | 5V 5A High-Power USB-C Receptacle (Power Delivery to Pi 5) | Amphenol ICC | **12401610E4#2A** | Mouser: `523-12401610E42A` |
| 24 | `J6` | Proposed 12V barrel output (not compatible with the selected 5V media converter)| CUI Devices | **PJ-002AH-SMT-TR** | Mouser: `490-PJ-002AH-SMT-TR` |
| 25 | `J7` | 12V PTC De-Icing Heater Ring Terminal (Molex Micro-Fit 3.0, 2-Pin) | Molex | **43650-0200** | Mouser: `538-43650-0200` |
| 26 | `TB1` | Geophone Differential Input Terminal (2-Pin 5.08mm Screw Terminal) | Phoenix Contact / COTS | **MKDSN 1,5/ 2-5,08** | LCSC: `C474952` |

---

## 4. Mechanical & Climate Weatherproofing Subsystem

| Item | Description | Manufacturer | Manufacturer Part Number | Supplier / Distributor |
|---|---|---|---|---|
| 27 | Industrial Polycarbonate Enclosure (IP66, IK10, $-40^\circ\text{C}$ to $+80^\circ\text{C}$) | **Fibox Oy (Espoo, Finland)** | **Fibox ARCA 302015** | Onninen FI / SLO / Yleiselektroniikka |
| 28 | Galvanized Steel Internal Mounting Plate ($250 \times 150\,\text{mm}$) | Fibox Oy | **MP ARCA 3020** | Onninen FI / Elfa Distrelec |
| 29 | M12 ePTFE Waterproof Pressure Equalization Vent (IP68, $-40^\circ\text{C}$) | Wiska Hoppmann | **VentGLAND M12 (EVMS 12)** | Elfa Distrelec: `301-44-122` |
| 30 | M20 IP68 Cable Glands with Low-Temp Silicone Seals ($-50^\circ\text{C}$ to $+100^\circ\text{C}$)| Lapp Group | **SKINTOP MS-M-XL 20x1.5** | Partco / Farnell FI: `1339832` |
| 31 | 12V 1.5W Ceramic PTC Lens De-Icing Ring ($25\,\text{mm}$ ID) | DBK Group / COTS | **PTC-RING-12V-1.5W** | Farnell FI / Mouser Europe |
| 32 | Conformal Coating Spray (Acrylic, IPC-CC-830 Industrial Spec) | HumiSeal | **HumiSeal 1B31** | Farnell FI: `1665873` |
| 33 | Outdoor Armored Single-Mode Fiber Cable (PUR, CSTA, $-45^\circ\text{C}$) | Prysmian Draka (Finland) | **Draka Boreal Flextreme SM** | Onninen Finland / SLO Oy |

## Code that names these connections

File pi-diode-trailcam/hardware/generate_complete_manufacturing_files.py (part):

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    ("U2", 1): "UART0_TX_PICO",
    ("U2", 2): "UART0_RX_PICO",
    ("U2", 3): "GND",
    ("U2", 4): "PI5_DONE",
    ("U2", 6): "I2C0_SDA",
    ("U2", 7): "I2C0_SCL",
    ("U2", 8): "GND",
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    ("U2", 19): "GEOPHONE_ALERT",
    ("U2", 20): "GATE_CTRL_DOMAIN_B",
    ("U2", 21): "GATE_CTRL_DEICE",
    ("U2", 22): "PI5_DONE",
    ("U2", 23): "GND",
    ("U2", 28): "GND",
    ("U2", 33): "GND",
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    ("J6", 1): "+12V_SWITCHED", ("J6", 2): "GND", ("J6", 3): "GND",

    # Pi 5 Telemetry & Handshake
    ("J4", 1): "PI5_UART_RX", ("J4", 2): "PI5_DONE", ("J4", 3): "+3V3_ALWAYS_ON", ("J4", 4): "GND",
    ("R2", 1): "TELEMETRY_TX", ("R2", 2): "PI5_UART_RX",
    ("R1", 1): "PI5_DONE", ("R1", 2): "GND",
    ("D5", 1): "PI5_UART_RX", ("D5", 2): "GND", ("D5", 3): "PI5_DONE", ("D5", 4): "PI5_DONE", ("D5", 5): "+3V3_ALWAYS_ON", ("D5", 6): "PI5_UART_RX",

    # Magnetometer I2C Bus
    ("J2", 1): "+3V3_SENSORS", ("J2", 2): "GND", ("J2", 3): "I2C0_SDA", ("J2", 4): "I2C0_SCL",
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        ("I2C0_SCL", [(46.11, 62.0), (24.0, 62.0), p("U4", 10)], 0.35),
        # Pi 5 Telemetry
        ("TELEMETRY_TX", [p("U2", 11), (46.11, 52.0), (80.0, 52.0), p("R2", 1)], 0.35),
        ("PI5_UART_RX", [p("R2", 2), p("D5", 1), p("J4", 1)], 0.35),
        # Pi 5 Handshake
        ("PI5_DONE", [p("J4", 2), p("D5", 3), p("R1", 1), (80.0, 36.0), (63.89, 36.0), p("U2", 22)], 0.35),
        ("PI5_DONE", [(80.0, 36.0), (46.11, 36.0), p("U2", 4)], 0.35),
        # Geophone Differential
        ("GEOPHONE_P", [p("TB1", 1), p("D4", 1), p("U4", 4)], 0.35),
        ("GEOPHONE_N", [p("TB1", 2), p("D4", 3), p("U4", 5)], 0.35),
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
